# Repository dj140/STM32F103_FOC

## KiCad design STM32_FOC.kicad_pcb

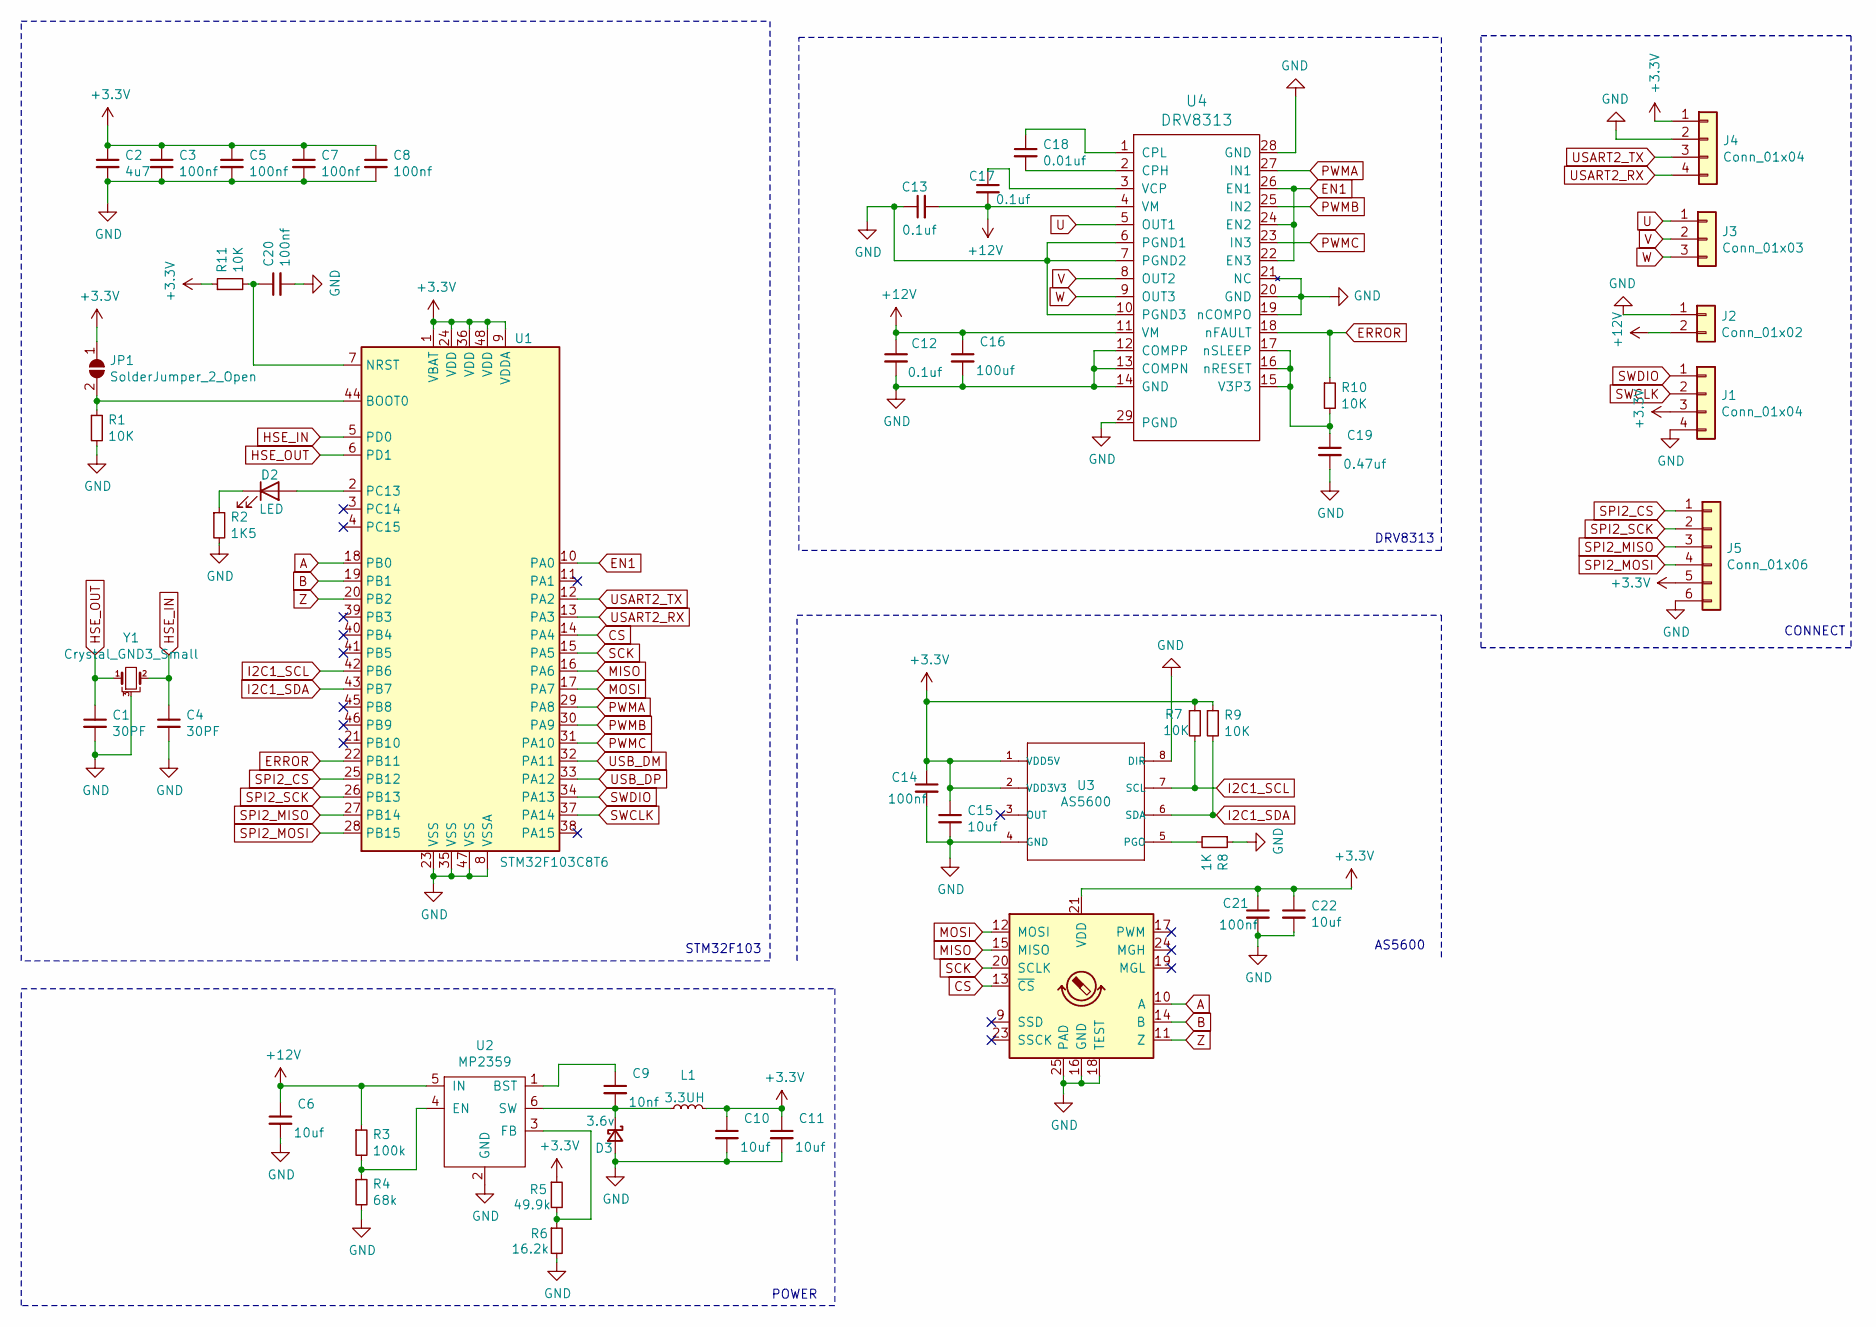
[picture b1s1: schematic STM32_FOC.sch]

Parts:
C1, C4: 30PF; C_0402_1005Metric
C2: 4u7; C_0402_1005Metric
C3, C5, C7, C8, C14, C20, C21: 100nf; C_0402_1005Metric
C6, C15, C22: 10uf; C_0603_1608Metric
C9: 10nf; C_0402_1005Metric
C10, C11: 10uf; C_0402_1005Metric
C12: 0.1uf; C_0603_1608Metric
C13, C17: 0.1uf; C_0402_1005Metric
C16: 100uf; C_1206_3216Metric
C18: 0.01uf; C_0402_1005Metric
C19: 0.47uf; C_0402_1005Metric
D2: LED; LED_0402_1005Metric
D3: 3.6v; D_SOD-123
J1, J4: Conn_01x04; JST_SH_SM04B-SRSS-TB_1x04-1MP_P1.00mm_Horizontal
J2: Conn_01x02; JST_SH_SM02B-SRSS-TB_1x02-1MP_P1.00mm_Horizontal
J3: Conn_01x03; PinHeader_1x03_P2.54mm_Vertical
J5: Conn_01x06; JST_SH_SM06B-SRSS-TB_1x06-1MP_P1.00mm_Horizontal
JP1: SolderJumper_2_Open; SoldJumper-2-P0.5mm_Open_RoundedPad
L1: 3.3UH; L_0420
R1, R7, R9, R10, R11: 10K; R_0402_1005Metric
R2: 1K5; R_0402_1005Metric
R3: 100k; R_0402_1005Metric
R4: 68k; R_0402_1005Metric
R5: 49.9k; R_0402_1005Metric
R6: 16.2k; R_0402_1005Metric
R8: 1K; R_0402_1005Metric
U1: STM32F103C8T6; LQFP-48_7x7mm_P0.5mm
U2: MP2359; SOT-23-6
U3: AS5600
U4: DRV8313; SquantorTexasInstruments-HTSSOP-28
Y1: Crystal_GND3_Small; CSTCE8M00G55-R0

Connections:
+3V3: C2.1, C3.1, C5.1, C7.1, C8.1, C10.1, C11.1, C14.1, C15.1, C21.1, C22.1, J1.3, J4.1, J5.5, JP1.1 (A), L1.2, R5.1, R7.1, R9.1, R11.1, U1.1 (VBAT), U1.9 (VDDA), U1.24 (VDD), U1.36 (VDD), U1.48 (VDD), U3.1 (VDD5V), U3.2 (VDD3V3), U3.21 (VDD)
+12V: C6.1, C12.1, C13.2, C16.1, C17.2, J2.2, R3.1, U2.5 (IN), U4.4 (VM), U4.11 (VM)
A: U1.18 (PB0), U3.10 (A)
B: U1.19 (PB1), U3.14 (B)
CS: U1.14 (PA4), U3.13 (~CS)
EN1: U1.10 (PA0), U4.22 (EN3), U4.24 (EN2), U4.26 (EN1)
ERROR: R10.1, U1.22 (PB11), U4.18 (nFAULT)
GND: C1.2, C2.2, C3.2, C4.2, C5.2, C6.2, C7.2, C8.2, C10.2, C11.2, C12.2, C13.1, C14.2, C15.2, C16.2, C19.2, C20.2, C21.2, C22.2, D3.2 (A), J1.4, J2.1, J4.2, J5.6, R1.2, R2.2, R4.2, R6.2, R8.1, U1.8 (VSSA), U1.23 (VSS), U1.35 (VSS), U1.47 (VSS), U2.2 (GND), U3.4 (GND), U3.8 (DIR), U3.16 (GND), U3.18 (TEST), U3.25 (PAD), U4.6 (PGND1), U4.7 (PGND2), U4.10 (PGND3), U4.12 (COMPP), U4.13 (COMPN), U4.14 (GND), U4.19 (nCOMPO), U4.20 (GND), U4.21 (NC), U4.28 (GND), U4.29 (PGND), Y1.3
HSE_IN: C4.1, U1.5 (PD0), Y1.2
HSE_OUT: C1.1, U1.6 (PD1), Y1.1
I2C1_SCL: R7.2, U1.42 (PB6), U3.7 (SCL)
I2C1_SDA: R9.2, U1.43 (PB7), U3.6 (SDA)
MISO: U1.16 (PA6), U3.15 (MISO)
MOSI: U1.17 (PA7), U3.12 (MOSI)
unnamed: C9.1, U2.1 (BST)
unnamed: C9.2, D3.1 (K), L1.1, U2.6 (SW)
unnamed: C17.1, U4.3 (VCP)
unnamed: C18.1, U4.1 (CPL)
unnamed: C18.2, U4.2 (CPH)
unnamed: C19.1, R10.2, U4.15 (V3P3), U4.16 (nRESET), U4.17 (nSLEEP)
unnamed: C20.1, R11.2, U1.7 (NRST)
unnamed: D2.1 (K), R2.1
unnamed: D2.2 (A), U1.2 (PC13)
unnamed: JP1.2 (B), R1.1, U1.44 (BOOT0)
unnamed: R3.2, R4.1, U2.4 (EN)
unnamed: R5.2, R6.1, U2.3 (FB)
unnamed: R8.2, U3.5 (PGO)
PWMA: U1.29 (PA8), U4.27 (IN1)
PWMB: U1.30 (PA9), U4.25 (IN2)
PWMC: U1.31 (PA10), U4.23 (IN3)
SCK: U1.15 (PA5), U3.20 (SCLK)
SPI2_CS: J5.1, U1.25 (PB12)
SPI2_MISO: J5.3, U1.27 (PB14)
SPI2_MOSI: J5.4, U1.28 (PB15)
SPI2_SCK: J5.2, U1.26 (PB13)
SWCLK: J1.2, U1.37 (PA14)
SWDIO: J1.1, U1.34 (PA13)
U: J3.1, U4.5 (OUT1)
USART2_RX: J4.4, U1.13 (PA3)
USART2_TX: J4.3, U1.12 (PA2)
USB_DM: U1.32 (PA11)
USB_DP: U1.33 (PA12)
V: J3.2, U4.8 (OUT2)
W: J3.3, U4.9 (OUT3)
Z: U1.20 (PB2), U3.11 (Z)

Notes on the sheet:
STM32F103
AS5600
DRV8313
POWER
CONNECT

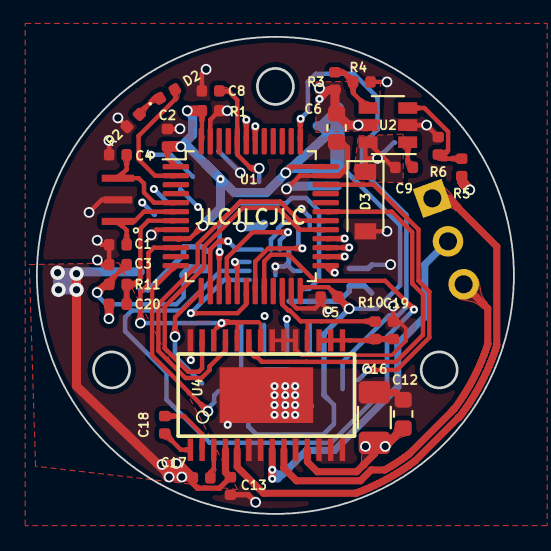
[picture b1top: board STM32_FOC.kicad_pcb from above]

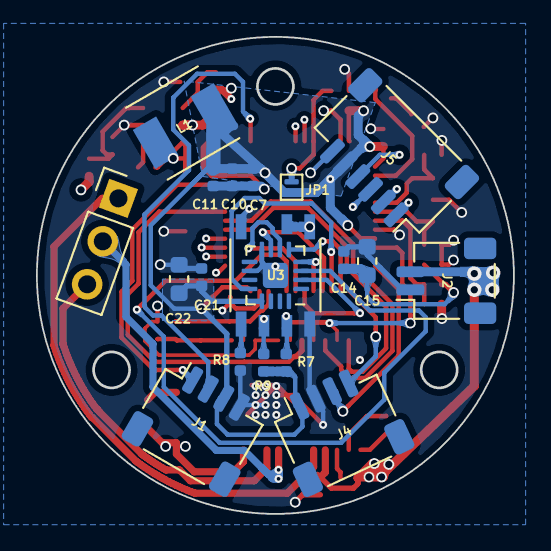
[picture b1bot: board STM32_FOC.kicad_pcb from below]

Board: 4 copper layers, 26.4 x 26.4 mm, 47 parts (18 on the bottom side), 43 nets.

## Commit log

2021-08-01 updata
2021-10-30 fix some bugs
